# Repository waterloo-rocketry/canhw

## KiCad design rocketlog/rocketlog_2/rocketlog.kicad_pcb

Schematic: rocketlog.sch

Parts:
C1, C2: 0.1u; C_0805_2012Metric_Pad1.15x1.40mm_HandSolder
C3: 10u; C_0805_2012Metric_Pad1.15x1.40mm_HandSolder
C4, C5: C_Small; C_0805_2012Metric_Pad1.15x1.40mm_HandSolder
C11: C; C_0805_2012Metric_Pad1.15x1.40mm_HandSolder
D1: DEBUG1; LED_1206_3216Metric_Pad1.42x1.75mm_HandSolder
D2: DEBUG2; LED_1206_3216Metric_Pad1.42x1.75mm_HandSolder
J1: Conn_01x05_Female; PinHeader_5x2.54_SMD_90deg_952-3198-1-ND
R1: 10K; R_0805_2012Metric_Pad1.15x1.40mm_HandSolder
R3, R4: 330; R_0805_2012Metric_Pad1.15x1.40mm_HandSolder
U1: DSPIC33EP512GP502; SOIC-28W_7.5x17.9mm_P1.27mm
U2: MCP2562; SOIC-8_3.9x4.9mm_P1.27mm
Y1: Crystal; Crystal_HC49-4H_Vertical

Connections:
+3V3: C1.1, C2.2, J1.4, R1.1, U1.13 (VDD), U1.28 (AVDD), U2.5 (VIO); also elsewhere on the board
+5V: C11.1, R3.1, R4.1, U2.3 (VDD); also elsewhere on the board
/CANRX: U1.21 (TDO/RP42/RB10), U2.4 (RXD)
/CANTX: U1.22 (TDI/RP43/RB11), U2.1 (TXD)
/ICSPCLK: J1.1, U1.6 (PGEC1/AN4/C1IN1+/RPI34/RB2)
/ICSPDAT: J1.2, U1.7 (PGED1/AN5/C1IN1-/RP35/RB3)
/OSC1: C4.1, U1.9 (OSC1/CLKI/RA2), Y1.1
/OSC2: C5.1, U1.10 (OSC2/CLKO/RA3), Y1.2
/SD1_CS: U1.18 (TMS/ASDA1/SDI1/RP41/RB9); also elsewhere on the board
/SD1_MISO: U1.15 (PGEC2/ASCL2/RP38/RB6); also elsewhere on the board
/SD1_MOSI: U1.17 (TCK/CVREF1O/ASCL1/SDO1/RP40/T4CK/RB8); also elsewhere on the board
/SD1_SCLK: U1.16 (SCK1/RP39/INT0/RB7); also elsewhere on the board
/~MCLR: J1.5, R1.2, U1.1 (~MCLR)
CANH: U2.7 (CANH); also elsewhere on the board
CANL: U2.6 (CANL); also elsewhere on the board
CURR_AMP: U1.3 (AN1/C2IN1+/RA1); also elsewhere on the board
GND: C1.2, C2.1, C3.2, C4.2, C5.2, C11.2, J1.3, U1.8 (VSS), U1.19 (VSS), U1.27 (AVSS), U2.2 (VSS), U2.8 (STBY); also elsewhere on the board
unnamed: C3.1, U1.20 (VCAP)
unnamed: D1.1 (K), U1.24 (RPI45/CTPLS/RB13)
unnamed: D1.2 (A), R3.2
unnamed: D2.1 (K), U1.25 (RPI46/T3CK/RB14)
unnamed: D2.2 (A), R4.2

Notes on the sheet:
Not all pins support peripheral output, which is required for MOSI, SCK, and CANTX. RP20 and RP35-43 are the ones that support peripheral ouptut

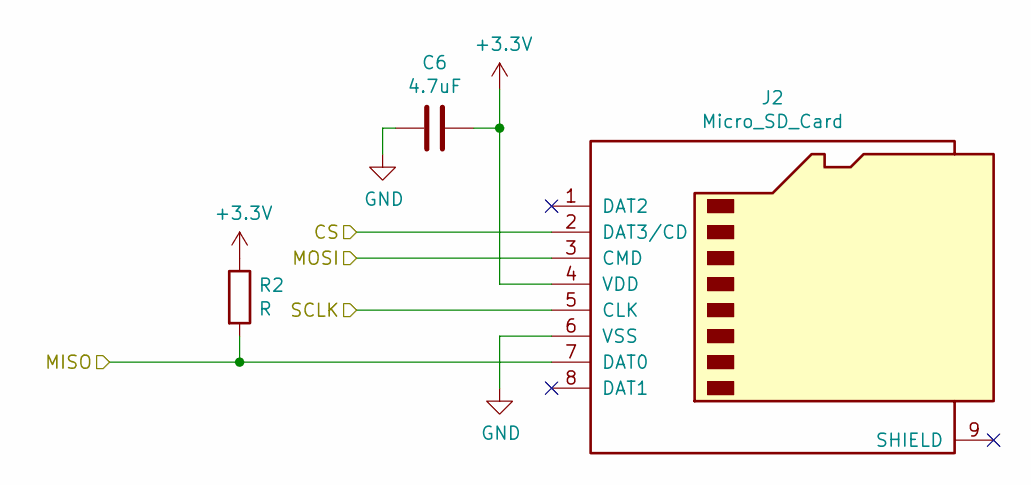
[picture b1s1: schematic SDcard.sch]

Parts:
C7: 4.7uF; C_0805_2012Metric_Pad1.15x1.40mm_HandSolder
J3: Micro_SD_Card; microSD_Molex_WM6698CT-ND
R2: R; R_0805_2012Metric_Pad1.15x1.40mm_HandSolder

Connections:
+3V3: R2.1; also elsewhere on the board
/SD1_MISO: R2.2; also elsewhere on the board

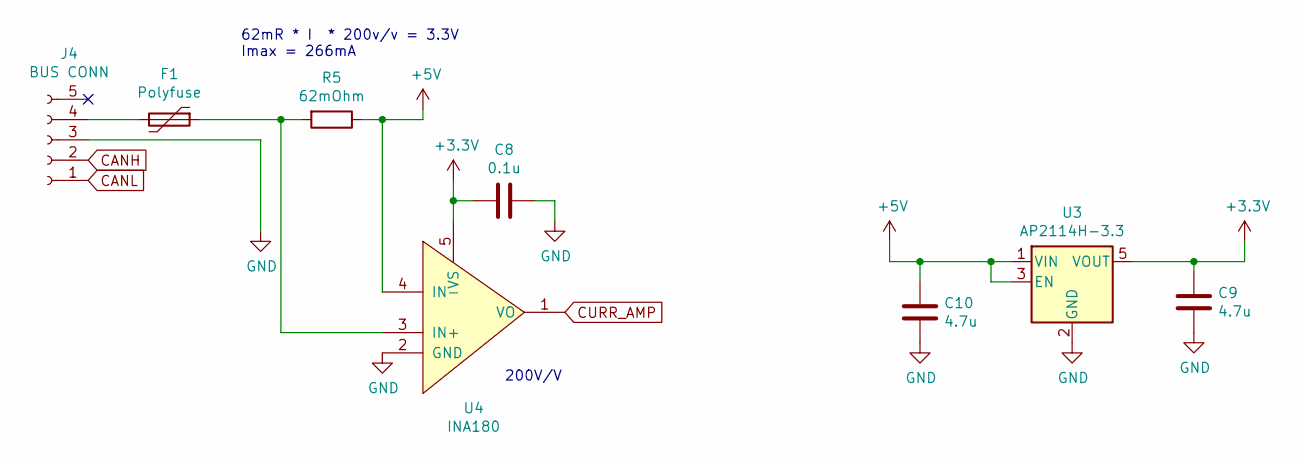
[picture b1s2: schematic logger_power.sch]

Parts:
C8: 0.1u; C_0805_2012Metric_Pad1.15x1.40mm_HandSolder
C9, C10: 4.7u; C_0805_2012Metric_Pad1.15x1.40mm_HandSolder
F1: Polyfuse; Fuse_1206_3216Metric_Pad1.42x1.75mm_HandSolder
J4: BUS CONN; connector_Harwin_M80-5000642
R5: 62mOhm; R_0805_2012Metric_Pad1.15x1.40mm_HandSolder
U3: AP2114H-3.3; SOT-23-5_HandSoldering
U4: INA180; SOT-23-5_HandSoldering

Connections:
+3V3: C8.2, C9.2, U3.5 (VOUT), U4.5 (VS); also elsewhere on the board
+5V: C10.2, R5.1, U3.1 (VIN), U3.3 (EN), U4.4 (IN-); also elsewhere on the board
CANH: J4.2; also elsewhere on the board
CANL: J4.1; also elsewhere on the board
CURR_AMP: U4.1 (VO); also elsewhere on the board
GND: C8.1, C9.1, C10.1, J4.3, U3.2 (GND), U4.2 (GND); also elsewhere on the board
unnamed: F1.1, R5.2, U4.3 (IN+)
unnamed: F1.2, J4.4

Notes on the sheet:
200V/V
62mR * I * 200v/v = 3.3V Imax = 266mA

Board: 2 copper layers, 26 parts (14 on the bottom side), 24 nets, no tracks yet.

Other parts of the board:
C6: 4.7uF; C_0805_2012Metric_Pad1.15x1.40mm_HandSolder
J2: Micro_SD_Card; microSD_Molex_WM6698CT-ND

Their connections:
+3V3: C6.1, J2.4; also elsewhere on the board
/SD1_CS: J2.2; also elsewhere on the board
/SD1_MISO: J2.7; also elsewhere on the board
/SD1_MOSI: J2.3; also elsewhere on the board
/SD1_SCLK: J2.5; also elsewhere on the board
GND: C6.2, J2.6; also elsewhere on the board

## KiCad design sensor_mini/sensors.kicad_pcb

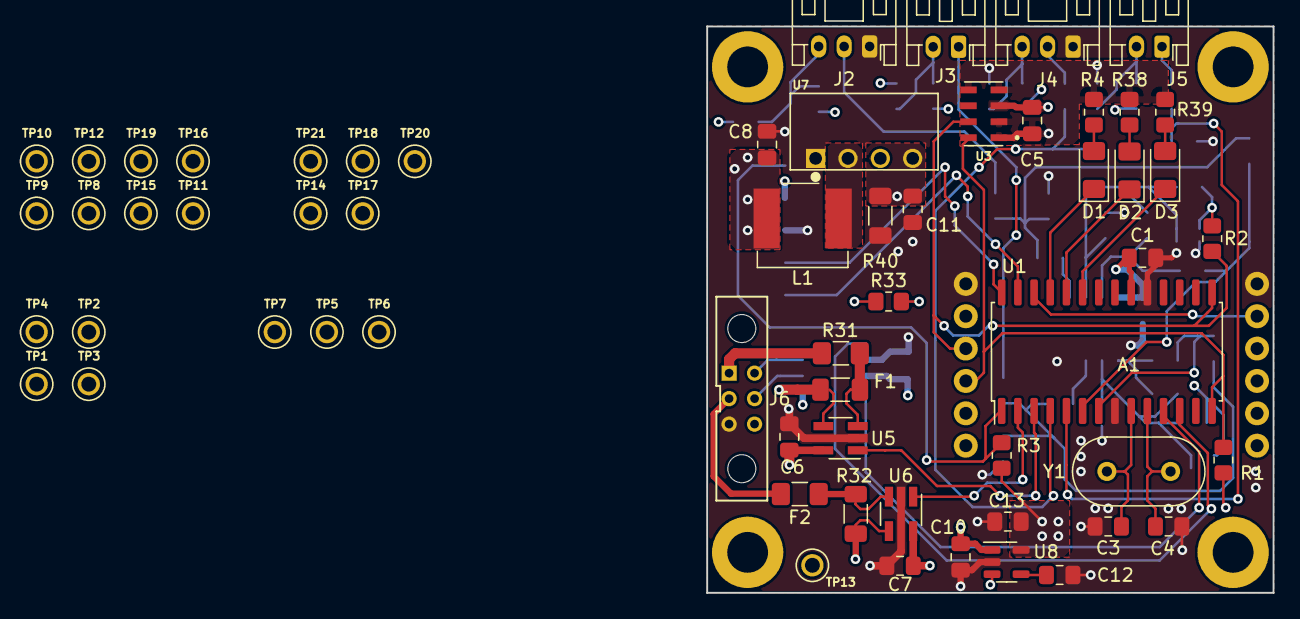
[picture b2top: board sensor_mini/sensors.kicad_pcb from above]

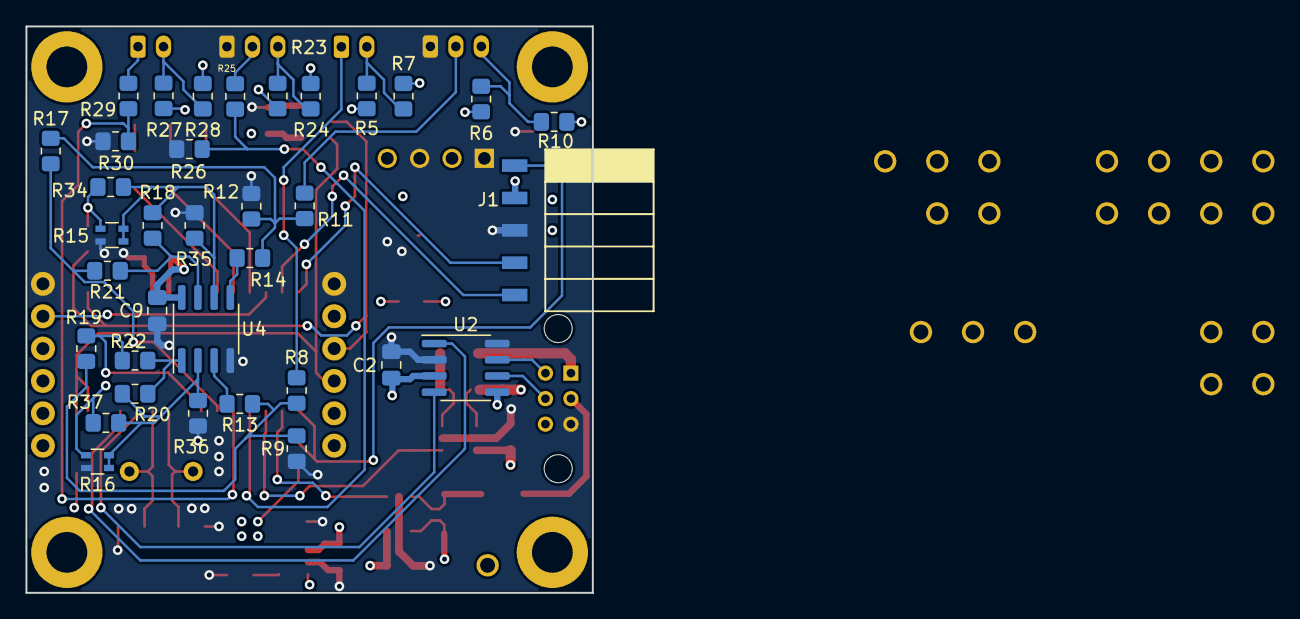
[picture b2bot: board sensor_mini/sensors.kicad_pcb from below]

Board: 4 copper layers, 44.5 x 44.5 mm, 96 parts (35 on the bottom side), 51 nets.

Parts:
A1: ICM-20948-Sparkfun-Daughtercard; IMU BB I2C
C1, C5, C6, C7: 0.1 uF; C_0805_2012Metric_Pad1.18x1.45mm_HandSolder
C2: 10 uF; C_0805_2012Metric_Pad1.18x1.45mm_HandSolder
C3, C4: 27 pF; C_0805_2012Metric_Pad1.18x1.45mm_HandSolder
C8: 4.7 uF; C_0805_2012Metric_Pad1.18x1.45mm_HandSolder
C9, C10: 1 uF; C_0805_2012Metric_Pad1.18x1.45mm_HandSolder
C11, C13: 2.2 uF; C_0805_2012Metric_Pad1.18x1.45mm_HandSolder
C12: 10 nF; C_0805_2012Metric_Pad1.18x1.45mm_HandSolder
D1: LED_GREEN; LED_1206_3216Metric_Pad1.42x1.75mm_HandSolder
D2: LED_BLUE; LED_1206_3216Metric_Pad1.42x1.75mm_HandSolder
D3: LED_WHITE; LED_1206_3216Metric_Pad1.42x1.75mm_HandSolder
F1, F2: Polyfuse 750 mA; Fuse_1206_3216Metric_Pad1.42x1.75mm_HandSolder
J1: Conn_01x05_Female-Connector; PinHeader_5x2.54_SMD_90deg_952-3198-1-ND
J2, J4: Conn_01x03_Female; JST_PH_S3B-PH-K_1x03_P2.00mm_Horizontal
J3, J5: Conn_01x02_Female-Connector; JST_PH_S2B-PH-K_1x02_P2.00mm_Horizontal
J6: Conn_01x05_Female-Connector; connector_Harwin_M80-5000642
L1: SRP0615-6R8K
R1, R2, R3: 10K; R_0805_2012Metric_Pad1.20x1.40mm_HandSolder
R4: 150R; R_0805_2012Metric_Pad1.20x1.40mm_HandSolder
R5, R6, R7, R10, R13, R14, R17, R19, R21, R22, R23, R24, R27, R28, R33: 0R; R_0805_2012Metric_Pad1.20x1.40mm_HandSolder
R8, R9, R11, R12, R18, R20, R25, R26, R29, R30: TBD; R_0805_2012Metric_Pad1.20x1.40mm_HandSolder
R15, R16: TBD; R_Array_Convex_2x0603
R31, R32: 200 mR; R_1206_3216Metric_Pad1.30x1.75mm_HandSolder
R34, R35, R36, R37: DNP; R_0805_2012Metric_Pad1.20x1.40mm_HandSolder
R38, R39: 330R; R_0805_2012Metric_Pad1.20x1.40mm_HandSolder
R40: 2.2K; R_1206_3216Metric_Pad1.30x1.75mm_HandSolder
TP1: TP_CANRX; KEYSTONE_5000
TP2: TP_CANTX; KEYSTONE_5000
TP3: TP_CANH; KEYSTONE_5000
TP4: TP_CANL; KEYSTONE_5000
TP5: TP_SCL; KEYSTONE_5000
TP6: TP_SDA; KEYSTONE_5000
TP7: TP_IMUINT; KEYSTONE_5000
TP8: TP_CH2AMP-SENS; KEYSTONE_5000
TP9: TP_CH1AMP-SENS; KEYSTONE_5000
TP10: TP_CH1AMP-REF; KEYSTONE_5000
TP11: TP_CH2AMP-REF; KEYSTONE_5000
TP12: TP_S1A-OUT; KEYSTONE_5000
TP13: TP_5V; KEYSTONE_5000
TP14: TP_12V; KEYSTONE_5000
TP15: TP_S2A-OUT; KEYSTONE_5000
TP16: TP_S3-OUT; KEYSTONE_5000
TP17: TP_3.3V; KEYSTONE_5000
TP18: TP_PWRSEL; KEYSTONE_5000
TP19: TP_S4-OUT; KEYSTONE_5000
TP20: CURRAMP5V; KEYSTONE_5000
TP21: CURRAMP12V; KEYSTONE_5000
U1: PIC18F26K83; SOIC-28W_7.5x17.9mm_P1.27mm
U2: MC2562; SOIC-8_3.9x4.9mm_P1.27mm
U3: MS5607-02BA03; SON125P300X500X100-8N
U4: TLV9002IDR; SOIC-8_3.9x4.9mm_P1.27mm
U5, U6: INA180; SOT-23-5_HandSoldering
U7: PDS1-S12-S15-S; CONV_PDS1-S12-S15-S
U8: SPX3819M5-L-3-3; SOT-23-5
Y1: Crystal; Resonator-2Pin_W10.0mm_H5.0mm

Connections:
12/15V_PWR: C11.1, R5.2, R6.2, R23.2, R27.2, R33.2, R40.2, TP18.1, U7.4 (+VO)
+3V3: A1.2 (VIN), A1.6 (~CS_VIN), A1.7 (VIN), C1.2, C5.2, C9.1, C13.1, J1.2, R1.1, R2.1, R3.1, R4.1, R7.2, R10.2, R15.1, R16.1, R24.2, R28.2, R34.2, R37.1, R38.1, R39.1, TP17.1, U1.20 (VDD), U2.5 (VIO), U3.1 (VDD), U3.2 (PS), U3.4 (CSB), U3.5 (CSB), U4.8 (V+), U8.5 (OUT)
+5V: C2.1, C6.2, C7.2, C10.1, R32.1, TP13.1, U2.3 (VDD), U5.5 (VS), U6.4 (IN-), U6.5 (VS), U8.1 (IN), U8.3 (EN)
+12V: C8.1, L1.1, R31.1, R33.1, TP14.1, U5.4 (IN-)
/Analog Sensors/SENSOR1_AMP_CAPABLE: R19.2, R22.2, TP12.1, U1.7 (RA5)
/Analog Sensors/SENSOR2_AMP_CAPABLE: R17.2, R21.2, TP15.1, U1.6 (RA4)
/Analog Sensors/SENSOR3_REGULAR: R25.1, R26.2, TP16.1, U1.4 (RA2)
/Analog Sensors/SENSOR4_REGULAR: R29.1, R30.2, TP19.1, U1.5 (RA3)
/Digital Sensor Suite/IMU_INT: A1.11 (INT_VIN), TP7.1, U1.26 (RB5)
/Digital Sensor Suite/SCL: A1.4 (SCL/SCLK_VIN), R1.2, TP5.1, U1.14 (RC3), U3.8 (SCLK)
/Digital Sensor Suite/SDA: A1.3 (SDA/SDI_VIN), R2.2, TP6.1, U1.15 (RC4), U3.7 (SDA)
/MCU/CAN_RX: TP1.1, U1.11 (RC0), U2.4 (RXD)
/MCU/CAN_TX: TP2.1, U1.12 (RC1), U2.1 (TXD)
/MCU/CURR_INPUT_5V: TP20.1, U1.2 (RA0), U6.1 (VO)
/MCU/CURR_INPUT_12V: TP21.1, U1.3 (RA1), U5.1 (VO)
/MCU/ICSPCLK: J1.5, U1.27 (RB6/ICSPCLK)
/MCU/ICSPDAT: J1.4, U1.28 (RB7/ICSPDAT)
/MCU/OSC1: C3.1, U1.9 (RA7/OSC1), Y1.1
/MCU/OSC2: C4.1, U1.10 (RA6/OSC2), Y1.2
/MCU/~MCLR: J1.1, R3.2, U1.1 (~MCLR)
CANH: J6.4, TP4.1, U2.7 (CANH)
CANL: J6.5, TP3.1, U2.6 (CANL)
GND: A1.1 (GND), A1.12 (GND), C1.1, C2.2, C3.2, C4.2, C5.1, C6.1, C7.1, C8.2, C9.2, C10.2, C11.2, C12.2, C13.2, J1.3, J2.1, J4.1, J6.3, R9.1, R12.2, R15.2, R16.2, R26.1, R30.1, R35.2, R36.1, R40.1, U1.8 (VSS), U1.19 (VSS), U2.2 (VSS), U2.8 (STBY), U3.3 (GND), U4.4 (V-), U5.2 (GND), U6.2 (GND), U7.1 (GND), U7.3 (0V), U8.2 (GND)
unnamed: C12.1, U8.4 (BP)
unnamed: D1.1 (K), U1.25 (RB4)
unnamed: D1.2 (A), R4.2
unnamed: D2.1 (K), U1.24 (RB3)
unnamed: D2.2 (A), R38.2
unnamed: D3.1 (K), U1.23 (RB2)
unnamed: D3.2 (A), R39.2
unnamed: F1.1, R31.2, U5.3 (IN+)
unnamed: F1.2, J6.1
unnamed: F2.1, R32.2, U6.3 (IN+)
unnamed: F2.2, J6.2
unnamed: J2.2, R11.1
unnamed: J2.3, R6.1, R10.1
unnamed: J3.1, R8.2
unnamed: J3.2, R5.1, R7.1
unnamed: J4.2, R25.2
unnamed: J4.3, R23.1, R24.1
unnamed: J5.1, R29.2
unnamed: J5.2, R27.1, R28.1
unnamed: L1.2, U7.2 (VIN)
unnamed: R11.2, R12.1, R14.1, R17.1, TP8.1
unnamed: R8.1, R9.2, R13.1, R19.1, TP9.1
unnamed: R13.2, U4.3
unnamed: R14.2, U4.5
unnamed: R15.3, R15.4, R18.1, R34.1, R35.1, TP11.1, U4.6
unnamed: R16.3, R16.4, R20.1, R36.2, R37.2, TP10.1, U4.2
unnamed: R18.2, R21.1, U4.7
unnamed: R20.2, R22.1, U4.1

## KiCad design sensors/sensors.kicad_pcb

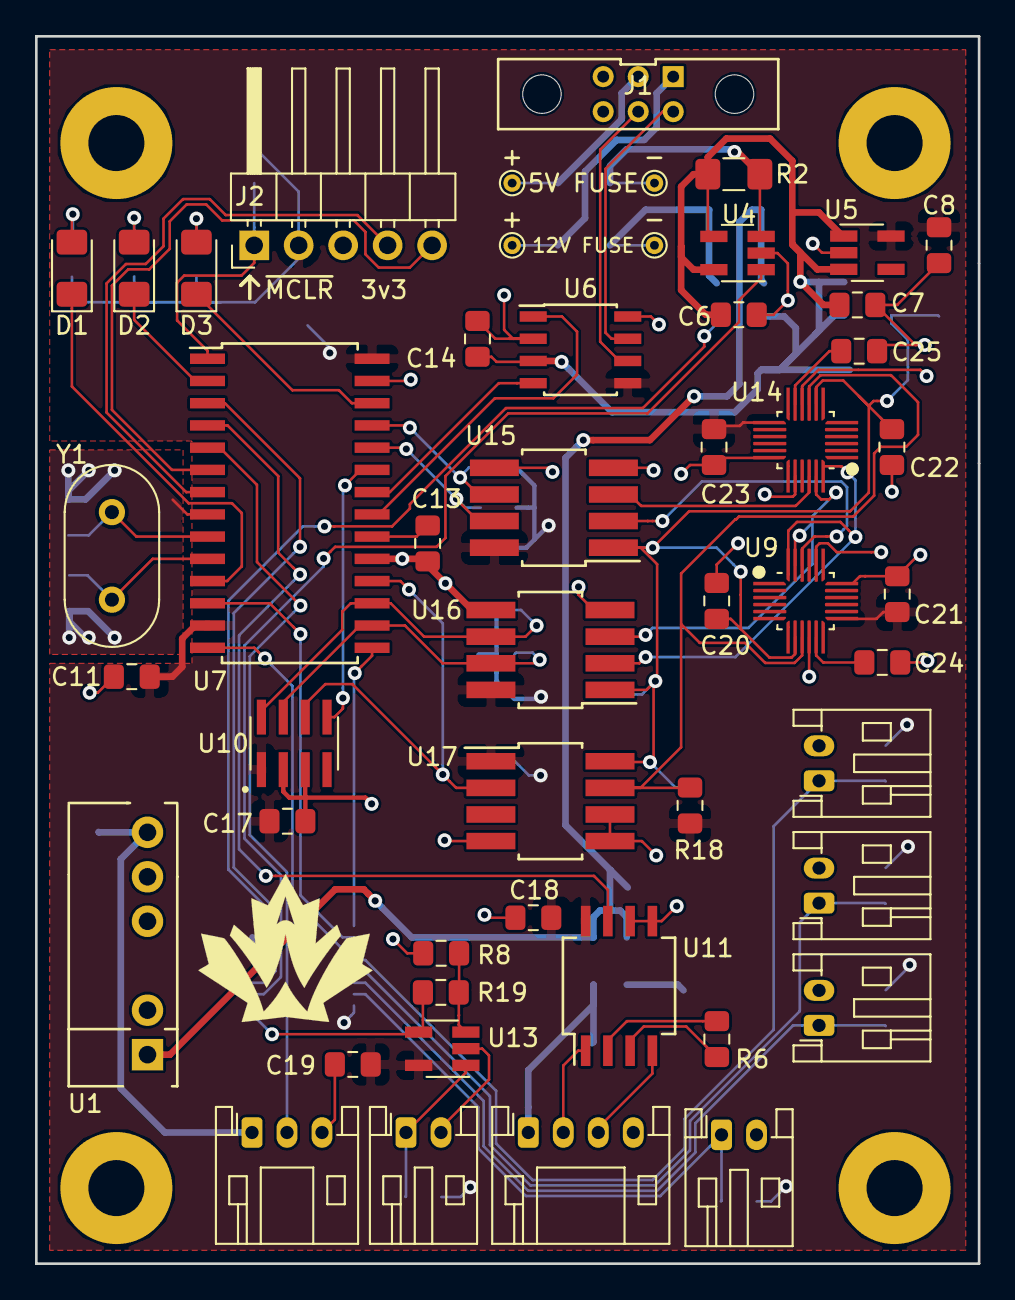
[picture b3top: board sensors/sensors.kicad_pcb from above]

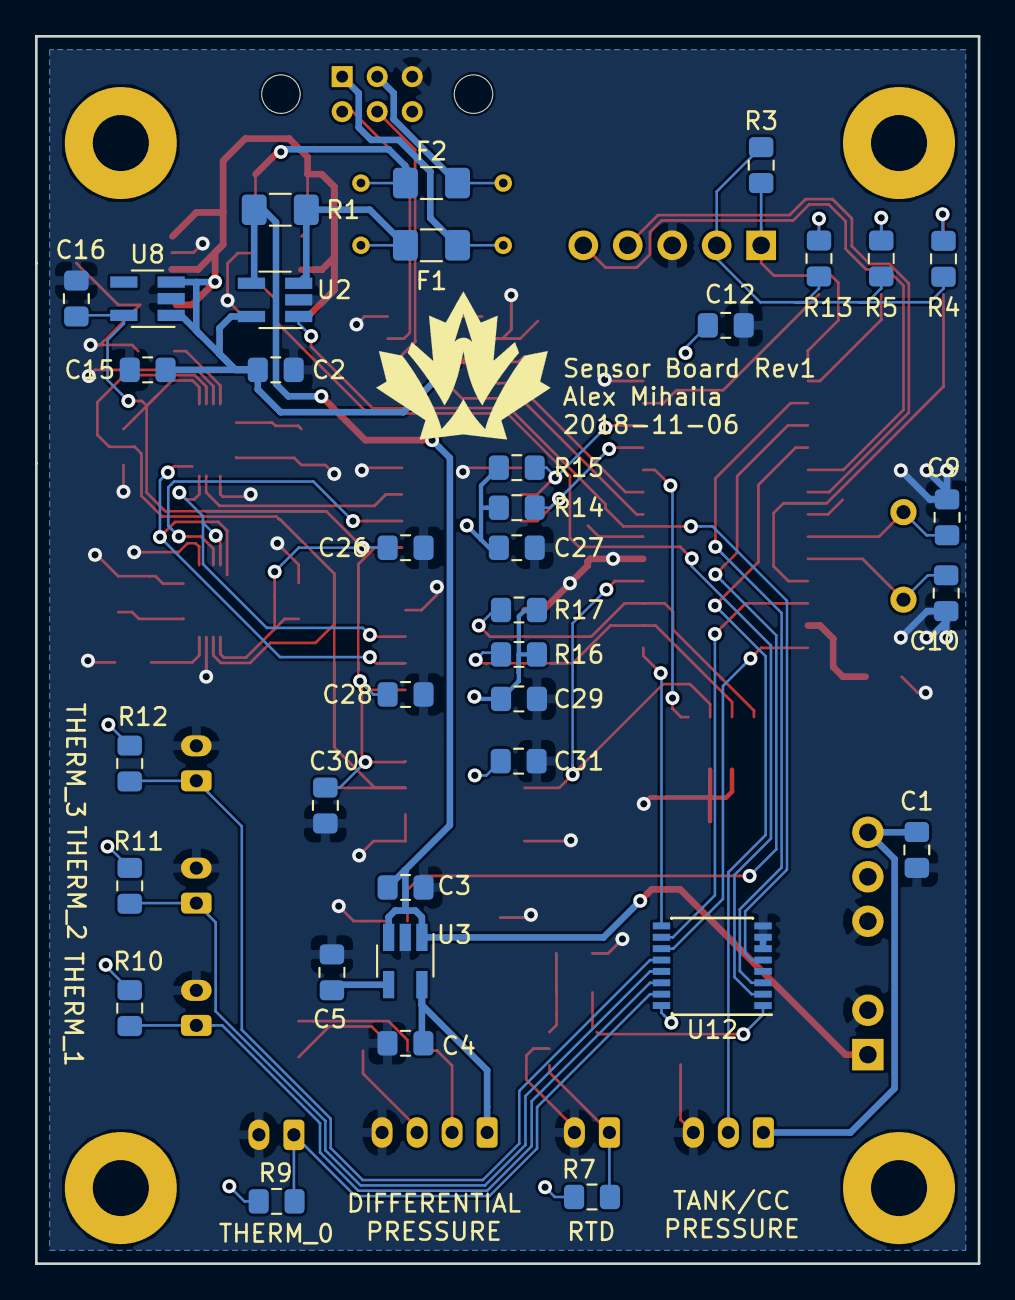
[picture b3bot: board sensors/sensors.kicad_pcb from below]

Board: 2 copper layers, 53.8 x 70.1 mm, 86 parts (36 on the bottom side), 60 nets.

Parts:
C1: 4.7uF; C_0805_2012Metric_Pad1.15x1.40mm_HandSolder
C2, C6, C11, C12, C17, C18, C19, C20, C21, C22, C23, C24, C25: 0.1uF; C_0805_2012Metric_Pad1.15x1.40mm_HandSolder
C3, C7, C8, C15, C16: 1uF; C_0805_2012Metric_Pad1.15x1.40mm_HandSolder
C4: 2.2uF; C_0805_2012Metric_Pad1.15x1.40mm_HandSolder
C5, C26, C27, C28, C29, C30, C31: 10nF; C_0805_2012Metric_Pad1.15x1.40mm_HandSolder
C9, C10: 26pF; C_0805_2012Metric_Pad1.15x1.40mm_HandSolder
C13, C14: 10uF; C_0805_2012Metric_Pad1.15x1.40mm_HandSolder
D1, D2, D3: LED; LED_1206_3216Metric_Pad1.42x1.75mm_HandSolder
F1, F2: Polyfuse; Fuse_1206_3216Metric_Pad1.42x1.75mm_HandSolder
J1: Conn_01x05_Female; connector_Harwin_M80-5000642
J2: Programming Header; PinHeader_1x05_P2.54mm_Horizontal
J3: Differential Pressure Conn; JST_PH_S4B-PH-K_1x04_P2.00mm_Horizontal
J4: RTD Conn; JST_PH_S2B-PH-K_1x02_P2.00mm_Horizontal
J5: Tank Pressure Conn; JST_PH_S3B-PH-K_1x03_P2.00mm_Horizontal
J6, J7, J8, J9: Thermistor Conn; JST_PH_S2B-PH-K_1x02_P2.00mm_Horizontal
R1: R_US; R_1206_3216Metric_Pad1.42x1.75mm_HandSolder
R2: ?; R_1206_3216Metric_Pad1.42x1.75mm_HandSolder
R3, R9, R10, R11, R12, R14, R15, R16, R17, R18: 10K; R_0805_2012Metric_Pad1.15x1.40mm_HandSolder
R4, R5, R13: 330R; R_0805_2012Metric_Pad1.15x1.40mm_HandSolder
R6, R7, R8, R19: R_US; R_0805_2012Metric_Pad1.15x1.40mm_HandSolder
TP1, TP2, TP3, TP4: TestPoint; TestPoint_THTPad_D1.0mm_Drill0.5mm
U1: SPU01M-15; SIP6_Housing
U2, U4: INA180; SOT-23-5_HandSoldering
U3: LP2985-10; SOT-23-5_HandSoldering
U5: MIC5504-3.3; SOT-23-5_HandSoldering
U6: MCP2562; SOIC-8_3.9x4.9mm_Pitch1.27mm
U7: DSPIC33EP512GP502; SOIC-28W_7.5x17.9mm_Pitch1.27mm
U8: MIC5365-1.8; SOT-23-5_HandSoldering
U9, U14: ICM-20948; QFN-24-1EP_3x3mm_P0.4mm_EP1.75x1.6mm_HandSoldering
U10: MS5607-02BA03; MS560702BA03
U11: INA826; SO-8_5.3x6.2mm_Pitch1.27mm
U12: 74HC4051D; SSOP-16_4.4x5.2mm_Pitch0.65mm
U13: MCP6001U; SOT-23-5_HandSoldering
U15, U16, U17: SN74LVC2T45; Zetex_SM8
Y1: Crystal; Resonator-2Pin_W10.0mm_H5.0mm

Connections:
+1V8: C16.1, C20.1, C22.1, C26.2, C28.2, C30.2, U8.5, U9.8, U14.8, U15.1, U16.1, U17.8
+3V3: C8.1, C11.1, C12.2, C17.2, C18.2, C19.2, C21.1, C23.1, C27.1, C29.1, C31.1, J2.2, R3.1, R4.1, R5.1, R7.1, R9.1, R10.1, R11.1, R12.1, R13.1, R14.1, R15.1, R16.1, R17.1, R18.1, U5.5, U6.5, U7.13, U7.28, U9.13, U10.1, U11.8, U12.16, U13.5, U14.13, U15.8, U16.8, U17.1
+5V: C2.2, C6.2, C7.1, C14.1, C15.1, R2.1, U2.5, U4.4, U4.5, U5.1, U5.3, U6.3, U8.1, U8.3
+10V: C4.1, J3.1, U3.5
+12V: C3.1, R1.1, U1.1, U2.4, U3.1, U3.3
+15V: C1.1, J5.1, U1.6
/Analog Sensor Suite/CURR_AMP_5V: U4.1, U12.2
/Analog Sensor Suite/CURR_AMP_12V: U2.1, U12.5
/Analog Sensor Suite/DIFF_PRESSURE: U7.4, U11.7
/Analog Sensor Suite/DIFF_S+: J3.3, U11.4
/Analog Sensor Suite/DIFF_S-: J3.2, U11.1
/Analog Sensor Suite/MUX_S0: U7.14, U12.11
/Analog Sensor Suite/MUX_S1: U7.12, U12.10
/Analog Sensor Suite/MUX_S2: U7.15, U12.9
/Analog Sensor Suite/PRESSURE_STD: J5.2, U7.5
/Analog Sensor Suite/RTD: R19.1, U12.1, U13.4
/Analog Sensor Suite/RTD_DIVIDER: J4.1, R7.2, U13.1
/Analog Sensor Suite/THERM_0: J6.1, R9.2, U12.15
/Analog Sensor Suite/THERM_1: J7.1, R10.2, U12.14
/Analog Sensor Suite/THERM_2: J8.1, R11.2, U12.13
/Analog Sensor Suite/THERM_3: J9.1, R12.2, U12.12
/Digital Sensor Suite/BARO_CS: U7.23, U10.5
/Digital Sensor Suite/IMU1_CS: R14.2, U7.24, U15.7
/Digital Sensor Suite/IMU1_CS_1v8: U9.22, U15.2
/Digital Sensor Suite/IMU2_CS: R15.2, U7.25, U15.6
/Digital Sensor Suite/IMU2_CS_1v8: U14.22, U15.3
/Digital Sensor Suite/MISO: U7.18, U10.6, U17.2
/Digital Sensor Suite/MISO_1v8: R18.2, U9.9, U14.9, U17.7
/Digital Sensor Suite/MOSI: R16.2, U7.16, U10.7, U16.7
/Digital Sensor Suite/MOSI_1v8: U9.24, U14.24, U16.2
/Digital Sensor Suite/SCLK: R17.2, U7.17, U10.8, U16.6
/Digital Sensor Suite/SCLK_1v8: U9.23, U14.23, U16.3
/MCU/ANALOG_MUX: U7.3, U12.3
/MCU/CAN_RX: U6.4, U7.22
/MCU/CAN_TX: U6.1, U7.21
/MCU/ICSPCLK: J2.5, U7.6
/MCU/ICSPDAT: J2.4, U7.7
/MCU/OSC1: C9.1, U7.9, Y1.1
/MCU/OSC2: C10.1, U7.10, Y1.2
/MCU/~MCLR: J2.1, R3.2, U7.1
CANH: J1.4, U6.7
CANL: J1.5, U6.6
GND: C1.2, C2.1, C3.2, C4.2, C5.2, C6.1, C7.2, C8.2, C9.2, C10.2, C11.2, C12.1, C13.2, C14.2, C15.2, C16.2, C17.1, C18.1, C19.1, C20.2, C21.2, C22.2, C23.2, C24.2, C25.2, C26.1, C27.2, C28.1, C29.2, C30.1, C31.2, J1.3, J2.3, J3.4, J4.2, J5.3, J6.2, J7.2, J8.2, J9.2, R8.2, U1.2, U1.4, U2.2, U3.2, U4.2, U5.2, U6.2, U6.8, U7.8, U7.19, U7.27, U8.2, U9.10, U9.18, U9.20, U10.2, U10.3, U11.5, U11.6, U12.6, U12.7, U12.8, U13.2, U14.10, U14.18, U14.20, U15.4, U15.5, U16.4, U16.5, U17.4, U17.5, U17.6
unnamed: C5.1, U3.4
unnamed: C13.1, U7.20
unnamed: C24.1, U9.11
unnamed: C25.1, U14.11
unnamed: D1.1, U7.11
unnamed: D1.2, R4.2
unnamed: D2.1, U7.2
unnamed: D2.2, R5.2
unnamed: D3.1, U7.26
unnamed: D3.2, R13.2
unnamed: F1.1, R1.2, TP2.1, U2.3
unnamed: F1.2, J1.1, TP1.1
unnamed: F2.1, R2.2, TP4.1, U4.3
unnamed: F2.2, J1.2, TP3.1
unnamed: R6.1, U11.2
unnamed: R6.2, U11.3
unnamed: R8.1, R19.2, U13.3

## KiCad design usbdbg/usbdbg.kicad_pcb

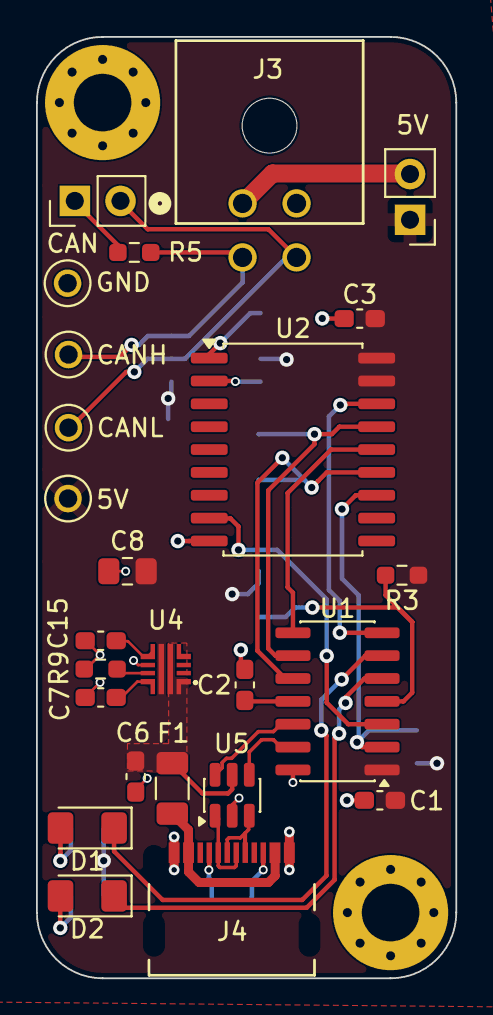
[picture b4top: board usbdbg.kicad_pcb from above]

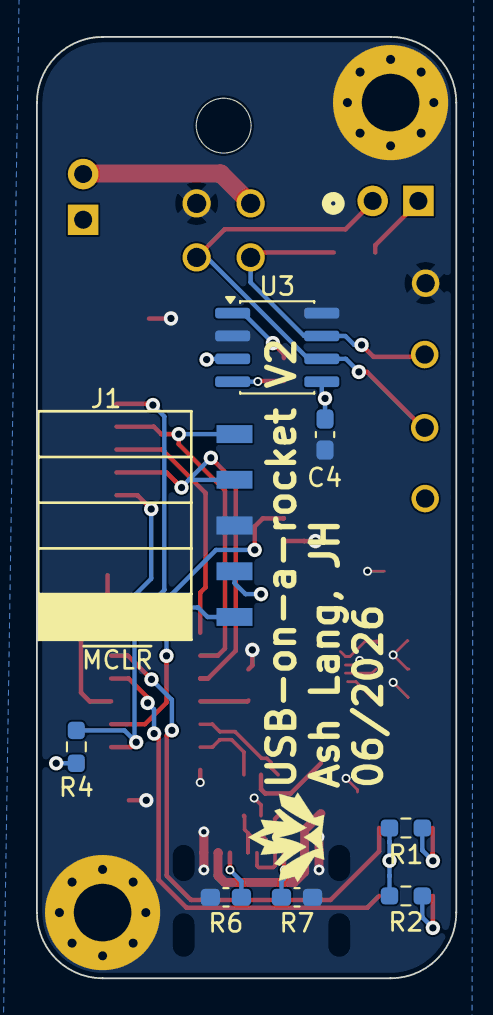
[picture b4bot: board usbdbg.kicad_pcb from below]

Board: 2 copper layers, 23.3 x 52.3 mm, 35 parts (8 on the bottom side), 31 nets.

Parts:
C1, C2, C3: 0.1u; C_0603_1608Metric_Pad1.08x0.95mm_HandSolder
C4: 10u; C_0603_1608Metric_Pad1.08x0.95mm_HandSolder
C6: 1uF; C_0603_1608Metric_Pad1.08x0.95mm_HandSolder
C7, C15: 10nF; C_0603_1608Metric_Pad1.08x0.95mm_HandSolder
C8: 10uF; C_0805_2012Metric_Pad1.18x1.45mm_HandSolder
D1: GREEN; LED_1206_3216Metric_Pad1.42x1.75mm_HandSolder
D2: RED; LED_1206_3216Metric_Pad1.42x1.75mm_HandSolder
F1: 1A; Fuse_1206_3216Metric
H1, H2: MountingHole_Pad; MountingHole_3.2mm_M3_Pad_Via
J1: Programming Header; PinSocket_5x2.54_SMD_90deg_952-3198-1-ND
J3: BUS CONN; CONN_SD-43045-001_04_MOL
J4: USB_C_Receptacle_USB2.0_14P; 2171790001_MOL
JP1, JP2: Jumper; PinHeader_1x02_P2.54mm_Vertical
R1, R2: 330R; R_0603_1608Metric_Pad0.98x0.95mm_HandSolder
R3, R4: 10k; R_0603_1608Metric_Pad0.98x0.95mm_HandSolder
R5: 120R; R_0603_1608Metric_Pad0.98x0.95mm_HandSolder
R6, R7: 5.1k; C_0603_1608Metric_Pad1.08x0.95mm_HandSolder
R9: 6.65k; R_0603_1608Metric_Pad0.98x0.95mm_HandSolder
TP1, TP2, TP3, TP4: TestPoint; KEYSTONE_5116
U1: PIC16F1455; SOIC-14_3.9x8.7mm_P1.27mm
U2: MCP2515; SOIC-18W_7.5x11.6mm_P1.27mm
U3: MCP2562; SOIC-8_3.9x4.9mm_P1.27mm
U4: TPS259472ARPW; TPS25947xx
U5: USBLC6-2SC6; SOT-23-6

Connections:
+5V: C1.1, C3.1, C4.1, C8.2, J1.2, JP2.1 (A), R1.2, R2.1, R3.1, R4.1, TP3.1 (1_1), U1.1 (VDD), U2.17 (~RESET), U2.18 (VDD), U3.3 (VDD), U3.5 (VIO), U4.6 (OUT)
/CANH: J3.3, R5.2, TP1.1 (1_1), U3.7 (CANH)
/CANL: J3.4, JP1.2 (B), TP2.1 (1_1), U3.6 (CANL)
/CAN_INT: R4.2, U1.2 (RA5), U2.12 (~INT)
/CLKOUT: U1.3 (RA4), U2.8 (OSC1)
/CS: U1.7 (RC3), U2.16 (~CS)
/ICSPCLK: J1.5, U1.9 (RC1/ICSPCLK), U2.15 (SO)
/ICSPDAT: J1.4, U1.10 (RC0/ICSPDAT), U2.13 (SCK)
/MOSI: U1.8 (RC2), U2.14 (SI)
/USB_D+: U1.13 (RA0/D+), U5.4 (I/O2)
/USB_D-: U1.12 (RA1/D-), U5.6 (I/O1)
/~MCLR: J1.1, R3.2, U1.4 (RA3/~MCLR)
GND: C1.2, C2.2, C3.2, C4.2, C6.1, C7.1, C8.1, C15.1, H1.1 (1_1), H2.1 (1_1), J1.3, J3.2, J4.A1 (GND), J4.A12 (GND), R6.2, R7.2, R9.2, TP4.1 (1_1), U1.14 (VSS), U2.9 (VSS), U3.2 (VSS), U3.8 (STBY), U4.8 (GND), U5.2 (GND)
unnamed: D1.2 (A), R1.1
unnamed: D1.1 (K), U1.6 (RC4)
unnamed: D2.2 (A), R2.2
unnamed: D2.1 (K), U1.5 (RC5)
unnamed: F1.2, J4.A4 (VBUS), J4.A9 (VBUS)
unnamed: J3.1, JP2.2 (B)
unnamed: J4.A5 (CC1), R7.1
unnamed: J4.B5 (CC2), R6.1
unnamed: J4.A6 (D+), J4.B6 (D+), U5.3 (I/O2)
unnamed: J4.A7 (D-), J4.B7 (D-), U5.1 (I/O1)
unnamed: JP1.1 (A), R5.1
unnamed: C2.1, U1.11 (VUSB3V3)
unnamed: U2.2 (RXCAN), U3.4 (RXD)
unnamed: U2.1 (TXCAN), U3.1 (TXD)
unnamed: C15.2, U4.7 (DVDT)
unnamed: C6.2, F1.1, U4.1 (EN/UVLO), U4.5 (IN), U5.5 (VBUS)
unnamed: R9.1, U4.9 (ILM)
unnamed: C7.2, U4.10 (ITIMER)

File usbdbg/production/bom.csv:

Designator,Footprint,Quantity,Value,LCSC Part #
"C1, C2, C3",0603,3,0.1u,
"C15, C7",0603,2,10nF,
C4,0603,1,10u,
C6,0603,1,1uF,
C8,0805,1,10uF,
D1,1206,1,GREEN,
D2,1206,1,RED,
F1,1206,1,1A,
J1,PinSocket_5x2.54_SMD_90deg_952-3198-1-ND,1,Programming Header,
J3,CONN_SD-43045-001_04_MOL,1,BUS CONN,
J4,2171790001_MOL,1,USB_C_Receptacle_USB2.0_14P,
"JP1, JP2",PinHeader_1x02_P2.54mm_Vertical,2,Jumper,
"R1, R2",0603,2,330R,
"R3, R4",0603,2,10k,
R5,0603,1,120R,
"R6, R7",0603,2,5.1k,
R9,0603,1,6.65k,
"TP1, TP2, TP3, TP4",KEYSTONE_5116,4,TestPoint,
U1,SOIC-14_3.9x8.7mm_P1.27mm,1,PIC16F1455,
U2,SOIC-18W_7.5x11.6mm_P1.27mm,1,MCP2515,
U3,SOIC-8_3.9x4.9mm_P1.27mm,1,MCP2562,
U4,TPS25947xx,1,TPS259472ARPW,
U5,SOT-23-6,1,USBLC6-2SC6,

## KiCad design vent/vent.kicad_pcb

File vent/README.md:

# Vent Board 

The purpose of the vent board is to open and close the valve that allows for nitrous oxide to flow into the rocket before launch. 

## Front of vent:

## Back of vent:

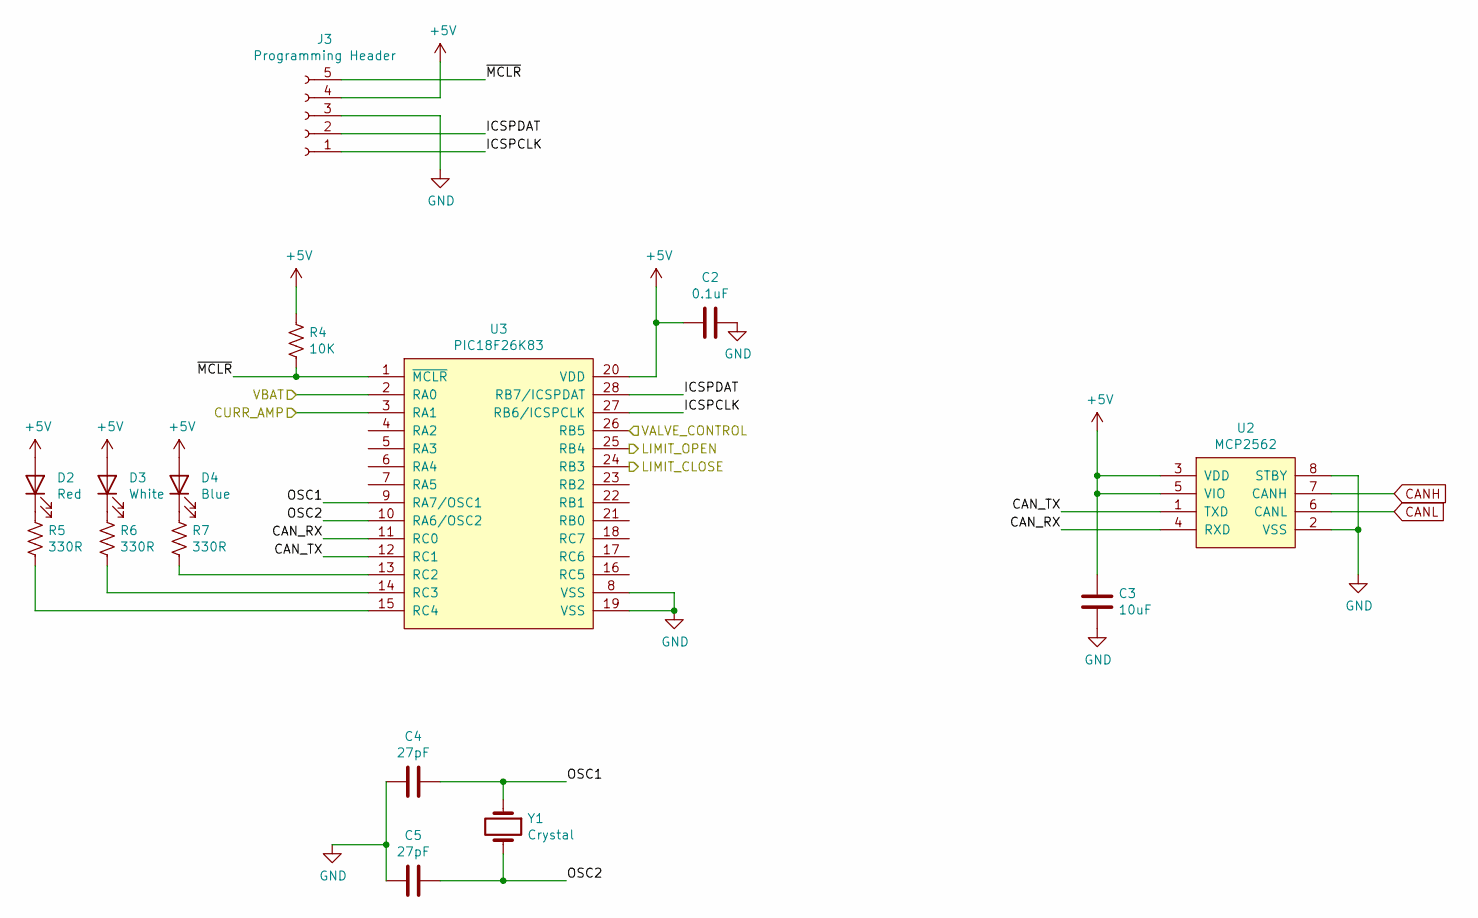
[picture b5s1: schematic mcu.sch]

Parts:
C2: 0.1uF; C_0805_2012Metric
C3: 10uF; C_0805_2012Metric_Pad1.15x1.40mm_HandSolder
C4, C5: 27pF; C_0805_2012Metric
D2: Red; LED_1206_3216Metric_Pad1.42x1.75mm_HandSolder
D3: White; LED_1206_3216Metric_Pad1.42x1.75mm_HandSolder
D4: Blue; LED_1206_3216Metric_Pad1.42x1.75mm_HandSolder
J3: Programming Header; PinHeader_5x2.54_SMD_90deg_952-3198-1-ND
R4: 10K; R_0805_2012Metric
R5, R6, R7: 330R; R_0805_2012Metric
U2: MCP2562; SOIC-8_3.9x4.9mm_P1.27mm
U3: PIC18F26K83; SOIC-28W_7.5x17.9mm_P1.27mm
Y1: Crystal; Crystal_HC49-4H_Vertical

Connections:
+5V: C2.2, C3.1, D2.2 (A), D3.2 (A), D4.2 (A), J3.4, R4.1, U2.3 (VDD), U2.5 (VIO), U3.20 (VDD); also elsewhere on the board
/MCU/CAN_RX: U2.4 (RXD), U3.11 (RC0)
/MCU/CAN_TX: U2.1 (TXD), U3.12 (RC1)
/MCU/CURR_AMP: U3.3 (RA1); also elsewhere on the board
/MCU/ICSPCLK: J3.1, U3.27 (RB6/ICSPCLK)
/MCU/ICSPDAT: J3.2, U3.28 (RB7/ICSPDAT)
/MCU/LIMIT_CLOSE: U3.24 (RB3); also elsewhere on the board
/MCU/LIMIT_OPEN: U3.25 (RB4); also elsewhere on the board
/MCU/OSC1: C4.1, U3.9 (RA7/OSC1), Y1.1
/MCU/OSC2: C5.2, U3.10 (RA6/OSC2), Y1.2
/MCU/VALVE_CONTROL: U3.26 (RB5); also elsewhere on the board
/MCU/VBAT: U3.2 (RA0); also elsewhere on the board
/MCU/~MCLR: J3.5, R4.2, U3.1 (~MCLR)
CANH: U2.7 (CANH); also elsewhere on the board
CANL: U2.6 (CANL); also elsewhere on the board
GND: C2.1, C3.2, C4.2, C5.1, J3.3, U2.2 (VSS), U2.8 (STBY), U3.8 (VSS), U3.19 (VSS); also elsewhere on the board
unnamed: D2.1 (K), R5.1
unnamed: D3.1 (K), R6.1
unnamed: D4.1 (K), R7.1
unnamed: R5.2, U3.15 (RC4)
unnamed: R6.2, U3.14 (RC3)
unnamed: R7.2, U3.13 (RC2)

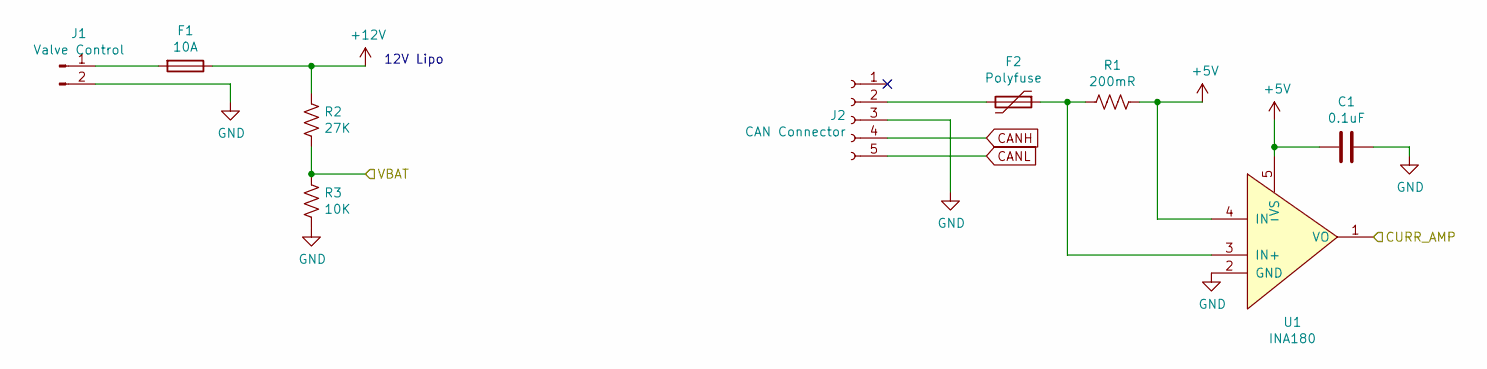
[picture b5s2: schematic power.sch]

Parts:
C1: 0.1uF; C_0805_2012Metric
F1: 10A; Fuseholder_36-3557-15-ND
F2: Polyfuse; Fuse_1206_3216Metric_Pad1.42x1.75mm_HandSolder
J1: Valve Control; JST_EH_B2B-EH-A_1x02_P2.50mm_Vertical
J2: CAN Connector; connector_Harwin_M80-5000642
R1: 200mR; R_1206_3216Metric
R2: 27K; R_0805_2012Metric
R3: 10K; R_0805_2012Metric
U1: INA180; SOT-23-5_HandSoldering

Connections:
+5V: C1.2, R1.1, U1.4 (IN-), U1.5 (VS); also elsewhere on the board
+12V: J2.1; also elsewhere on the board
/MCU/CURR_AMP: U1.1 (VO); also elsewhere on the board
/MCU/VBAT: R2.2, R3.1; also elsewhere on the board
CANH: J2.4; also elsewhere on the board
CANL: J2.5; also elsewhere on the board
GND: C1.1, J1.2, J2.3, R3.2, U1.2 (GND); also elsewhere on the board
unnamed 21: F1.2, J1.1; also elsewhere on the board
unnamed: F2.1, R1.2, U1.3 (IN+)
unnamed: F2.2, J2.2

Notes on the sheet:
12V Lipo

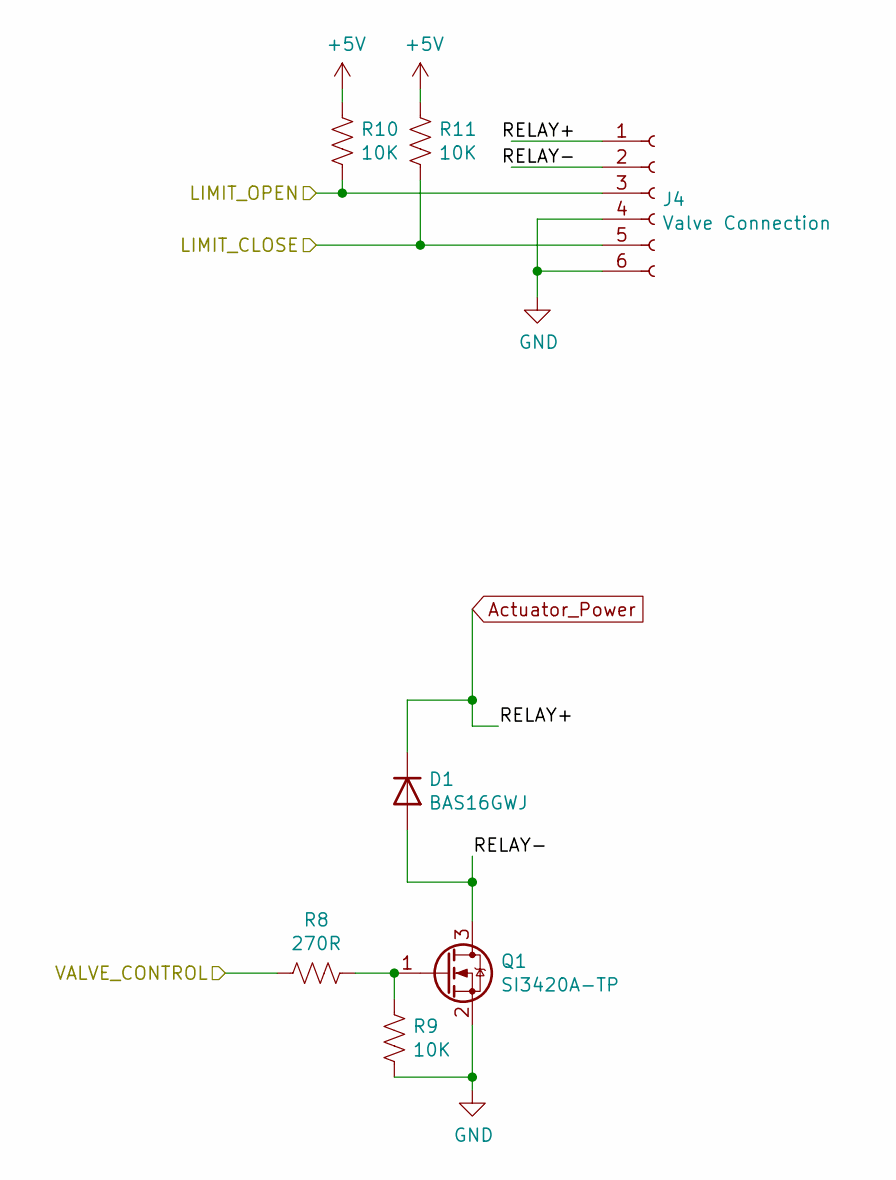
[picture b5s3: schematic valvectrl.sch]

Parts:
D1: BAS16GWJ; D_SOD-123
J4: Valve Connection; connector_Harwin_M80-5000642
Q1: SI3420A-TP; SOT-23_Handsoldering
R8: 270R; R_0805_2012Metric
R9, R10, R11: 10K; R_0805_2012Metric

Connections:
+5V: R10.1, R11.1; also elsewhere on the board
/MCU/LIMIT_CLOSE: J4.5, R11.2; also elsewhere on the board
/MCU/LIMIT_OPEN: J4.3, R10.2; also elsewhere on the board
/MCU/VALVE_CONTROL: R8.2; also elsewhere on the board
/Valve Control/RELAY-: D1.2 (A), J4.2, Q1.3 (D)
GND: J4.4, J4.6, Q1.2 (S), R9.2; also elsewhere on the board
unnamed: Q1.1 (G), R8.1, R9.1

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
